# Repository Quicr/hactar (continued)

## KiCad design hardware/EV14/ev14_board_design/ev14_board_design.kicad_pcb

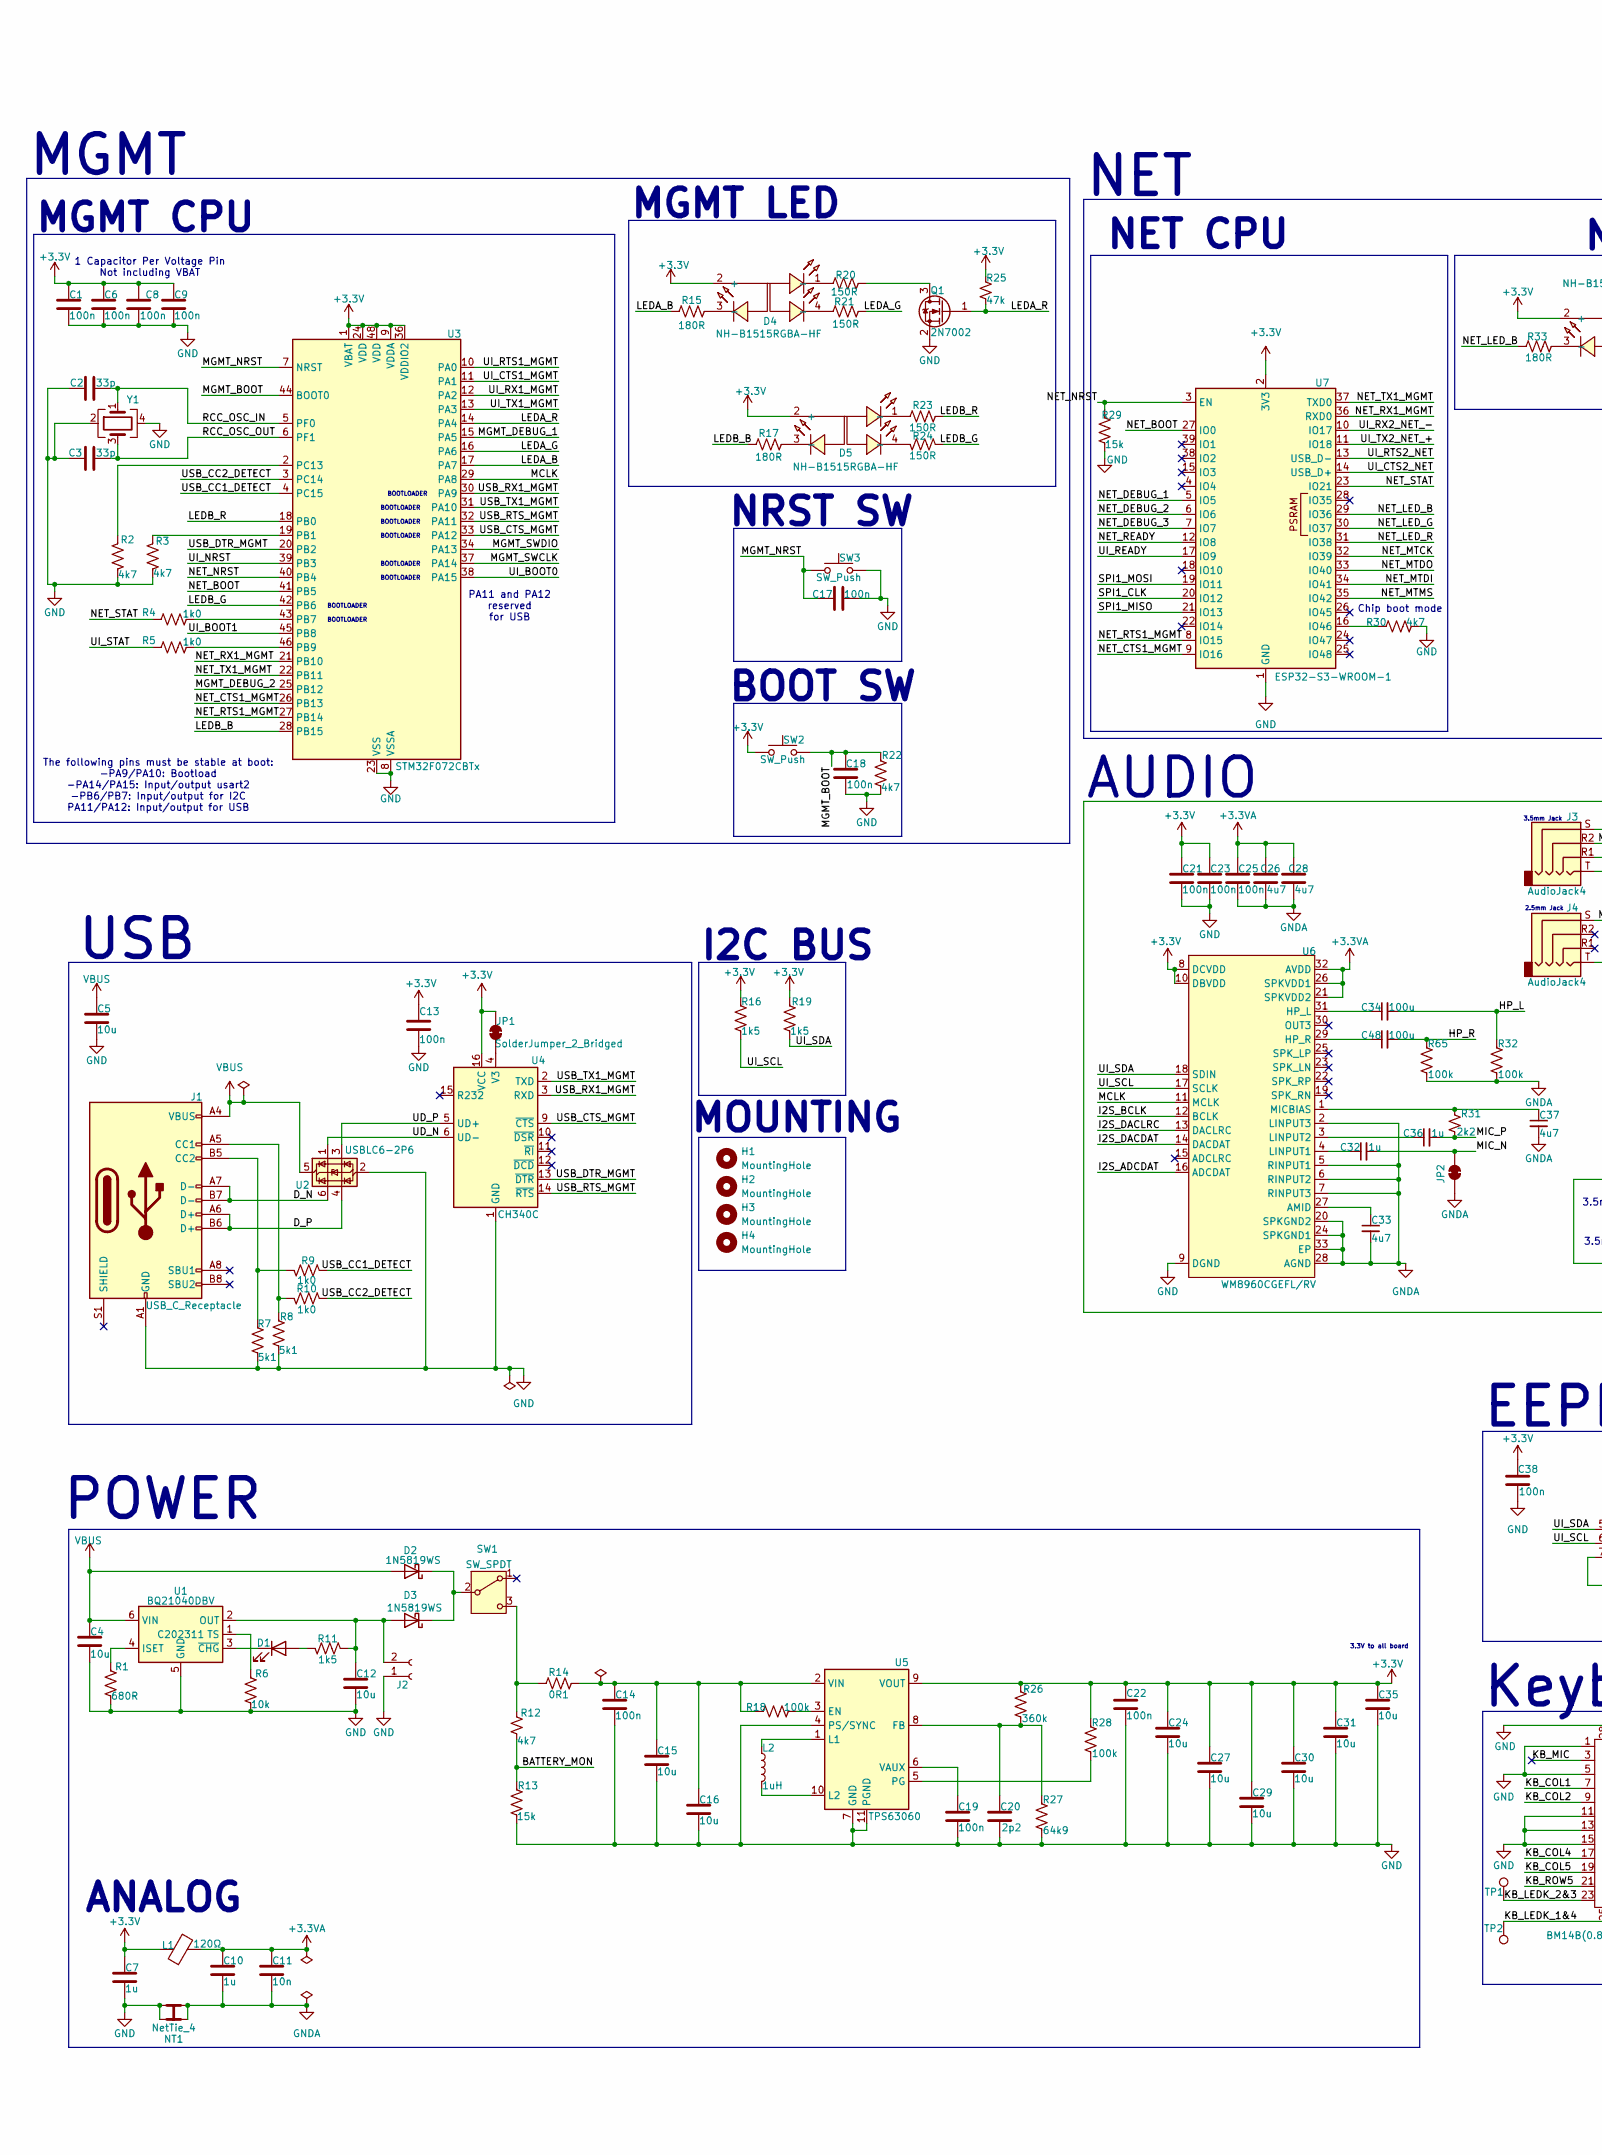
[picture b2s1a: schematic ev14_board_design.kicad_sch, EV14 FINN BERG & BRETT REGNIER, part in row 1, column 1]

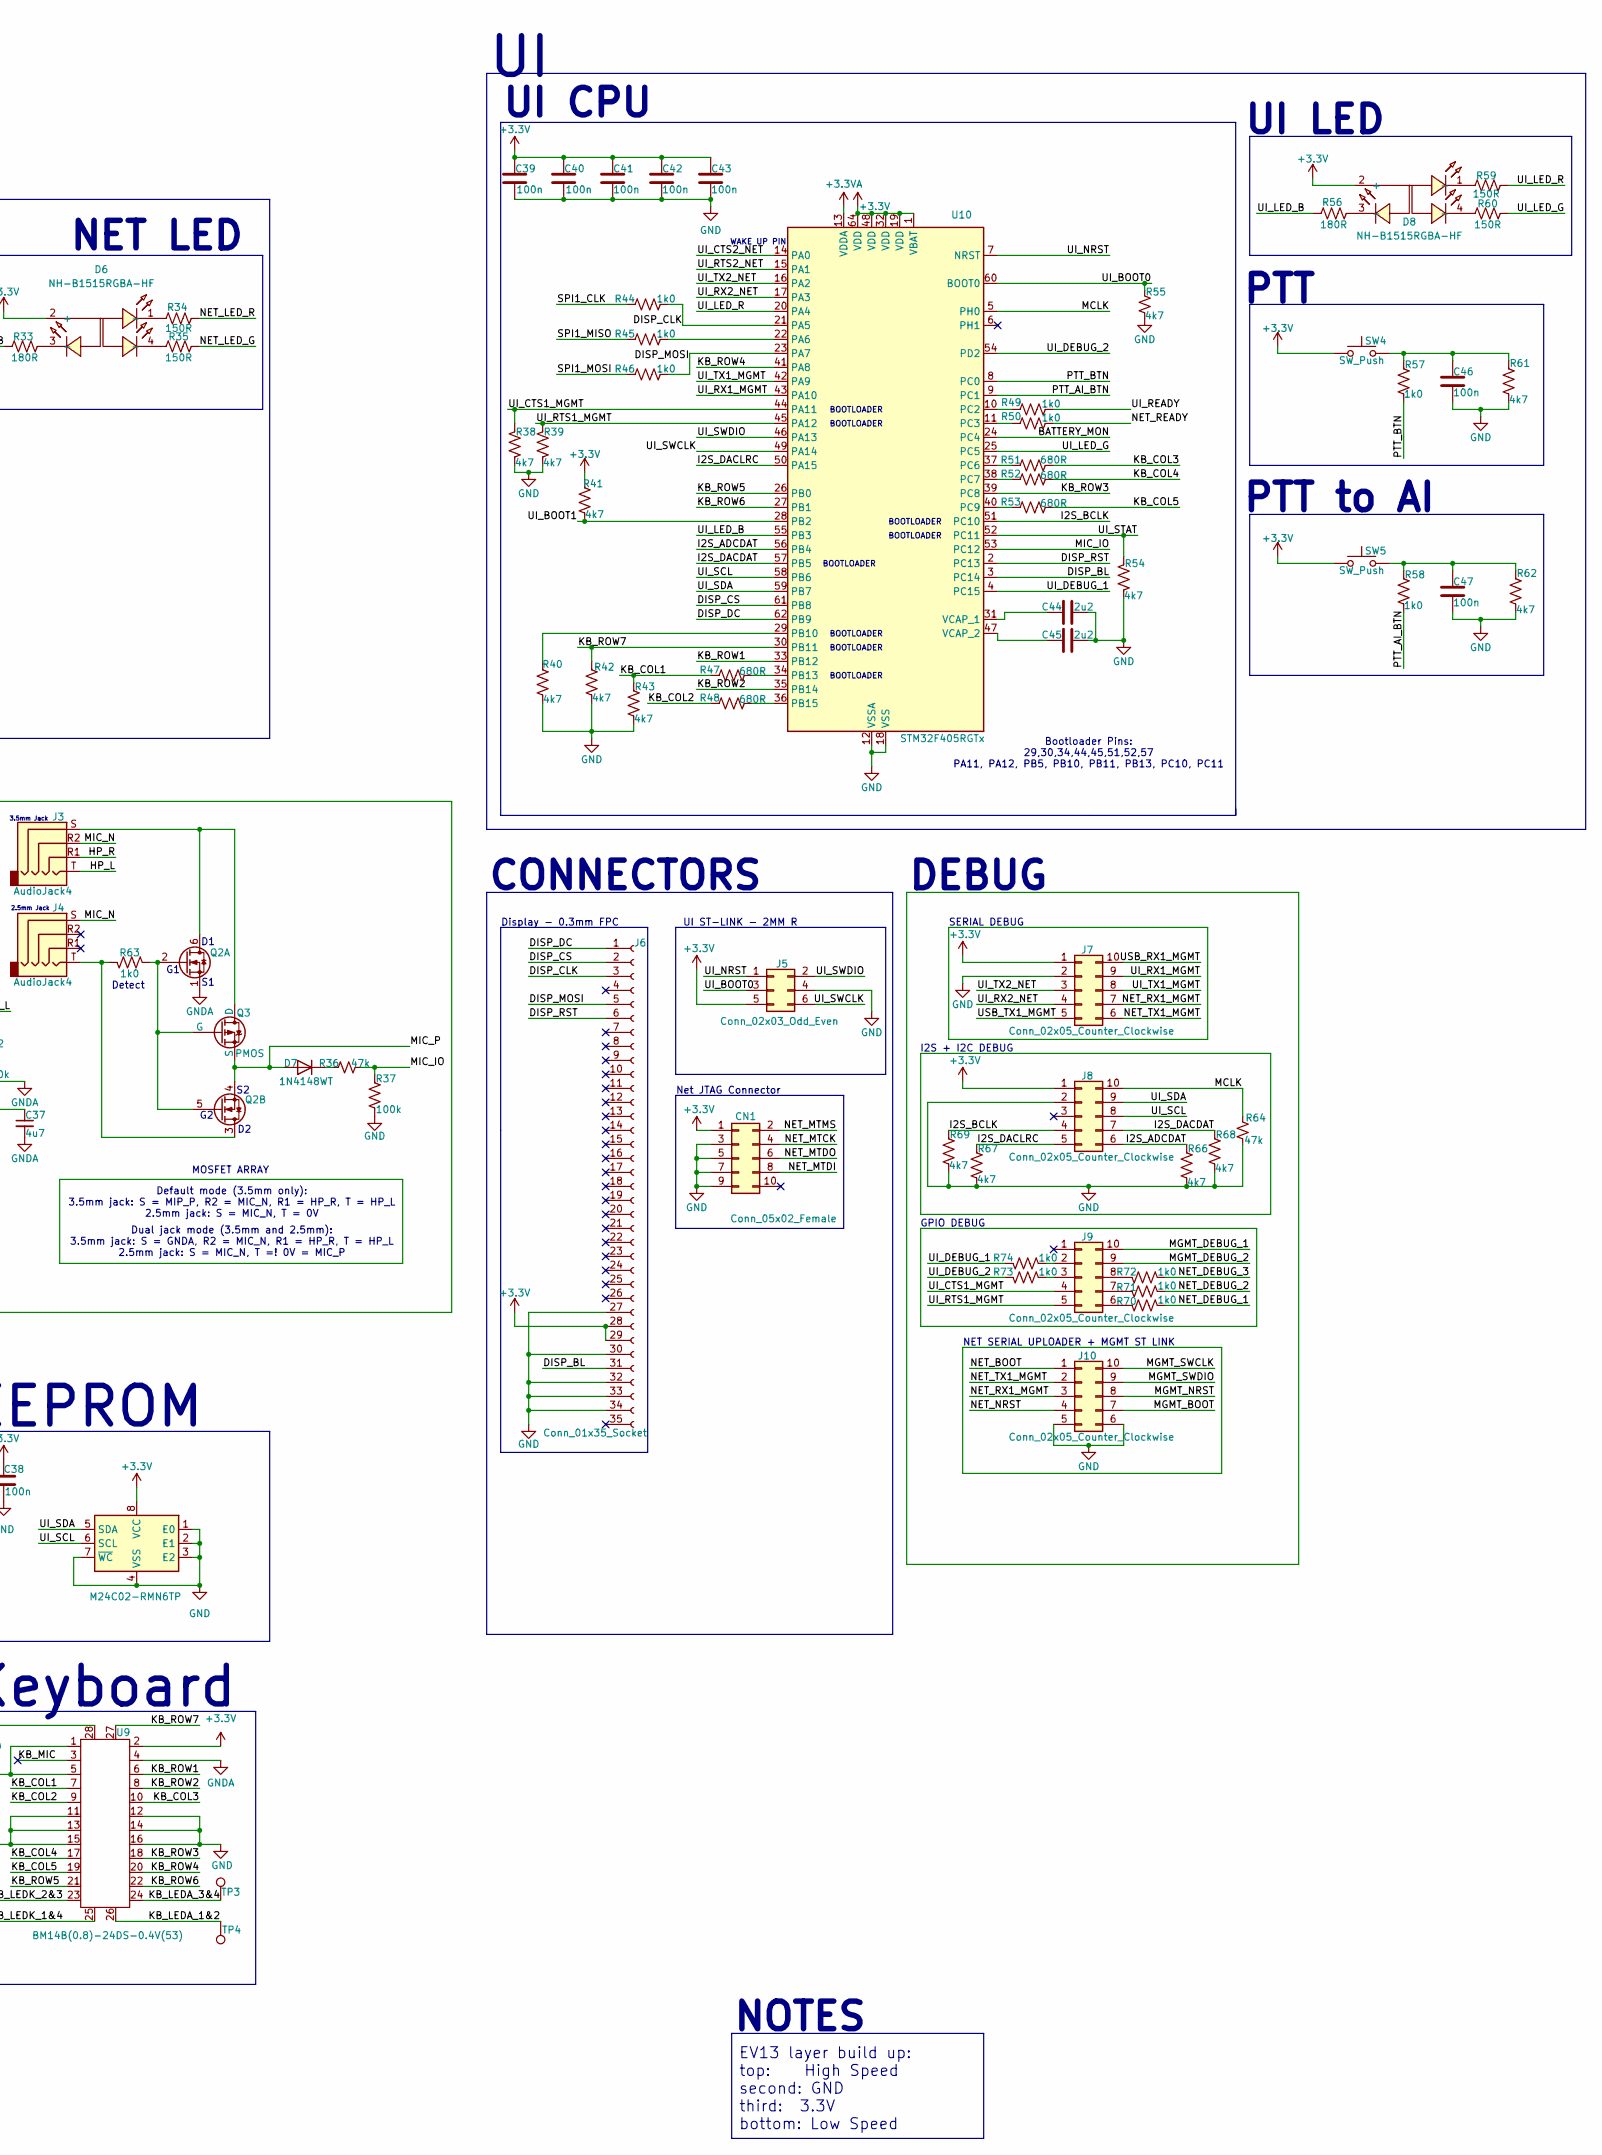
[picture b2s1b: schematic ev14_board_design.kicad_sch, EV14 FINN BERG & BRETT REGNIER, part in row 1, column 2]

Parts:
C1, C6, C8, C9, C13, C17, C18, C21, C23, C25, C38, C39, C40, C41, C42, C43, C46, C47: 100n; C_0402_1005Metric; JLCPCB Part # C1525
C2, C3: 33p; C_0805_2012Metric; JLCPCB Part # C107115
C4, C5, C12: 10u; C_0402_1005Metric; JLCPCB Part # C307415
C7, C10, C32, C36: 1u; C_0402_1005Metric; JLCPCB Part # C52923
C11: 10n; C_0402_1005Metric; JLCPCB Part # C15195
C14, C19, C22: 100n; C_0805_2012Metric; JLCPCB Part # C85866
C15, C16, C24, C27, C29, C30, C31, C35: 10u; C_0805_2012Metric; JLCPCB Part # C83061
C20: 2p2; C_0805_2012Metric; JLCPCB Part # C519933
C26, C28, C33, C37: 4u7; C_0402_1005Metric; JLCPCB Part # C23733
C34, C48: 100u; C_1206_3216Metric; JLCPCB Part # C15008
C44, C45: 2u2; C_0402_1005Metric; JLCPCB Part # C12530
CN1: Conn_05x02_Female; IDC-SMD_10P-P1.27_X1270WVS-2X05B-6TV01; JLCPCB Part # C2962222
D1: LED; D_0805_2012Metric; JLCPCB Part # C130114
D2, D3: 1N5819WS; D_SOD-323; JLCPCB Part # C191023
D4, D5, D6, D8: NH-B1515RGBA-HF; LED-ARRAY-SMD_4P-L1.6-W1.5-TL_NH-B1515RGBA; JLCPCB Part # C2874115
D7: 1N4148WT; D_SOD-523; JLCPCB Part # C27748
H1, H2, H3, H4: MountingHole; MountingHole_2.7mm_M2.5
J1: USB_C_Receptacle; USB-C_SMD-TYPE-C-31-M-12; JLCPCB Part # C165948
J2: Conn_01x02_Socket; JST_PH_S2B-PH-SM4-TB_1x02-1MP_P2.00mm_Horizontal; JLCPCB Part # C295747
J3: AudioJack4; AUDIO-SMD_PJ-320D; JLCPCB Part # C431535
J4: AudioJack4; AUDIO-SMD_PJ-242; JLCPCB Part # C431536
J5: Conn_02x03_Odd_Even; HDR-SMD_6P-P2.54-V-M-R2-C3-LS7.5-2; JLCPCB Part # C3294461
J6: Conn_01x35_Socket; CONN-SMD_HCTL_HC-FPC-03-09-35RLTAG; JLCPCB Part # C5213722
J7, J8, J9, J10: Conn_02x05_Counter_Clockwise; HDR-SMD_10P-P2.54-V-F-R2-C5-LS7.1-1; JLCPCB Part # C3975150
JP1: SolderJumper_2_Bridged; SolderJumper-2_P1.3mm_Bridged_RoundedPad1.0x1.5mm
JP2: SolderJumper_2_Bridged; NetTie-2_SMD_Pad0.5mm
L1: 120Ω; L_0603_1608Metric; JLCPCB Part # C127301
L2: 1uH; MCL2016A1R0MT; JLCPCB Part # C370013
NT1: NetTie_4; NetTie-4_SMD_Pad0.5mm
Q1: 2N7002; SOT-23; JLCPCB Part # C8545
Q2: Q_Dual_NMOS_S1G1D2S2G2D1; SOT-363_L2.1-W1.3-P0.65-LS2.3-BL; JLCPCB Part # C5362112
Q3: PMOS; SOT-23-3_L2.9-W1.3-P1.90-LS2.4-BR; JLCPCB Part # C181091
R1, R47, R48, R51, R52, R53: 680R; R_0402_1005Metric; JLCPCB Part # C25130
R2, R3, R12, R22, R30, R38, R39, R40, R41, R42, R43, R54, R55, R61, R62, R66, R67, R68, R69: 4k7; R_0402_1005Metric; JLCPCB Part # C25900
R4, R5, R9, R10, R44, R45, R46, R49, R50, R57, R58, R63, R70, R71, R72, R73, R74: 1k0; R_0402_1005Metric; JLCPCB Part # C11702
R6: 10k; R_0402_1005Metric; JLCPCB Part # C25744
R7, R8: 5k1; R_0402_1005Metric; JLCPCB Part # C25905
R11, R16, R19: 1k5; R_0402_1005Metric; JLCPCB Part # C25867
R13, R29: 15k; R_0402_1005Metric; JLCPCB Part # C25756
R14: 0R1; R_0603_1608Metric; JLCPCB Part # C111027
R15, R17, R33, R56: 180R; R_0402_1005Metric; JLCPCB Part # C25087
R18, R28, R32, R37, R65: 100k; R_0402_1005Metric; JLCPCB Part # C25741
R20, R21, R23, R24, R34, R35, R59, R60: 150R; R_0402_1005Metric; JLCPCB Part # C25082
R25, R36, R64: 47k; R_0402_1005Metric; JLCPCB Part # C25792
R26: 360k; R_0402_1005Metric; JLCPCB Part # C45956
R27: 64k9; R_0402_1005Metric; JLCPCB Part # C26984
R31: 2k2; R_0402_1005Metric; JLCPCB Part # C25879
SW1: SW_SPDT; SW-TH_SS-12D11G5R; JLCPCB Part # C388633
SW2, SW3: SW_Push; SW-SMD_YIYUAN_YTS1C003XXX; JLCPCB Part # C5188566
SW4, SW5: SW_Push; SW-SMD_L6.0-W6.0-LS6.6; JLCPCB Part # C97448
TP1, TP2, TP3, TP4: TestPoint; TestPoint_THTPad_D2.0mm_Drill1.0mm
U1: BQ21040DBV; SOT-23-6; JLCPCB Part # C202311
U2: USBLC6-2P6; SOT-666; JLCPCB Part # C2827693
U3: STM32F072CBTx; LQFP-48_7x7mm_P0.5mm; JLCPCB Part # C80488
U4: CH340C; SOIC-16_3.9x9.9mm_P1.27mm; JLCPCB Part # C84681
U5: TPS63060; Texas_S-PWSON-N10_ThermalVias; JLCPCB Part # C48567
U6: WM8960CGEFL/RV; QFN-32-1EP_5x5mm_P0.5mm_EP3.45x3.45mm_ThermalVias; JLCPCB Part # C18752
U7: ESP32-S3-WROOM-1; JLCPCB Part # C2913204
U8: M24C02-RMN6TP; SOIC-8_3.9x4.9mm_P1.27mm; JLCPCB Part # C83836
U9: BM14B(0.8)-24DS-0.4V(53); BM14B(0.B)-24DS-0.4V(53); JLCPCB Part # C9900001863
U10: STM32F405RGTx; LQFP-64_10x10mm_P0.5mm; JLCPCB Part # C15742
Y1: Crystal_GND24; Crystal_SMD_3225-4Pin_3.2x2.5mm; JLCPCB Part # C13738

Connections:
+3.3V: C1.2, C6.2, C7.1, C8.2, C9.2, C13.1, C21.2, C22.1, C23.2, C24.1, C27.1, C29.1, C30.1, C31.1, C35.1, C38.2, C39.1, C40.1, C41.1, C42.1, C43.1, CN1.1, D4.2 (+), D5.2 (+), D6.2 (+), D8.2 (+), J5.5, J6.28, J6.29, J7.1, J8.1, JP1.2 (B), L1.1, R16.1, R19.1, R25.2, R26.2, R28.2, R41.1, SW2.1, SW4.1, SW5.1, U3.1 (VBAT), U3.9 (VDDA), U3.24 (VDD), U3.36 (VDDIO2), U3.48 (VDD), U4.16 (VCC), U5.9 (VOUT), U6.8 (DCVDD), U6.10 (DBVDD), U7.2 (3V3), U8.8 (VCC), U9.2, U10.1 (VBAT), U10.19 (VDD), U10.32 (VDD), U10.48 (VDD), U10.64 (VDD)
+3.3VA: C10.1, C11.1, C25.2, C26.1, C28.1, L1.2, U6.21 (SPKVDD2), U6.26 (SPKVDD1), U6.32 (AVDD), U10.13 (VDDA)
/BATTERY_MON: R12.1, R13.1, U10.24 (PC4)
/DISP_BL: J6.31, U10.3 (PC14)
/DISP_CLK: J6.3, R44.1, U10.21 (PA5)
/DISP_CS: J6.2, U10.61 (PB8)
/DISP_DC: J6.1, U10.62 (PB9)
/DISP_MOSI: J6.5, R46.1, U10.23 (PA7)
/DISP_RST: J6.6, U10.2 (PC13)
/D_N: J1.A7 (D-), J1.B7 (D-), U2.6 (I/O1)
/D_P: J1.A6 (D+), J1.B6 (D+), U2.4 (I/O2)
/HP_L: C34.2, J3.T, R32.2
/HP_R: C48.2, J3.R1, R65.2
/I2S_ADCDAT: J8.6, R66.1, U6.16 (ADCDAT), U10.56 (PB4)
/I2S_BCLK: J8.4, R69.1, U6.12 (BCLK), U10.51 (PC10)
/I2S_DACDAT: J8.7, R68.1, U6.14 (DACDAT), U10.57 (PB5)
/I2S_DACLRC: J8.5, R67.1, U6.13 (DACLRC), U10.50 (PA15)
/KB_COL1: R43.2, R47.1, U9.7
/KB_COL2: R48.1, U9.9
/KB_COL3: R51.2, U9.10
/KB_COL4: R52.2, U9.17
/KB_COL5: R53.2, U9.19
/KB_LEDA_1&2: TP4.1, U9.26
/KB_LEDA_3&4: TP3.1, U9.24
/KB_LEDK_1&4: TP2.1, U9.25
/KB_LEDK_2&3: TP1.1, U9.23
/KB_MIC: U9.3
/KB_ROW1: U9.6, U10.33 (PB12)
/KB_ROW2: U9.8, U10.35 (PB14)
/KB_ROW3: U9.18, U10.39 (PC8)
/KB_ROW4: U9.20, U10.41 (PA8)
/KB_ROW5: U9.21, U10.26 (PB0)
/KB_ROW6: U9.22, U10.27 (PB1)
/KB_ROW7: R42.2, U9.27, U10.30 (PB11)
/LEDA_B: R15.2, U3.17 (PA7)
/LEDA_G: R21.2, U3.16 (PA6)
/LEDA_R: Q1.1 (G), R25.1, U3.14 (PA4)
/LEDB_B: R17.2, U3.28 (PB15)
/LEDB_G: R24.1, U3.42 (PB6)
/LEDB_R: R23.2, U3.18 (PB0)
/MCLK: J8.10, R64.1, U3.29 (PA8), U6.11 (MCLK), U10.5 (PH0)
/MGMT_BOOT: C18.2, J10.7, R22.2, SW2.2, U3.44 (BOOT0)
/MGMT_DEBUG_1: J9.10, U3.15 (PA5)
/MGMT_DEBUG_2: J9.9, U3.25 (PB12)
/MGMT_NRST: C17.1, J10.8, SW3.1, U3.7 (NRST)
/MGMT_SWCLK: J10.10, U3.37 (PA14)
/MGMT_SWDIO: J10.9, U3.34 (PA13)
/MIC_IO: R36.1, R37.2, U10.53 (PC12)
/MIC_N: C32.2, J3.R2, J4.S, JP2.1 (A)
/MIC_P: C36.2, D7.2 (A), Q2.4 (S), Q3.3 (S), R31.1
/NET_BOOT: J10.1, U3.41 (PB5), U7.27 (IO0)
/NET_CTS1_MGMT: U3.26 (PB13), U7.9 (IO16)
/NET_DEBUG_1: R70.1, U7.5 (IO5)
/NET_DEBUG_2: R71.1, U7.6 (IO6)
/NET_DEBUG_3: R72.1, U7.7 (IO7)
/NET_LED_B: R33.1, U7.29 (IO36)
/NET_LED_G: R35.1, U7.30 (IO37)
/NET_LED_R: R34.1, U7.31 (IO38)
/NET_MTCK: CN1.4, U7.32 (IO39)
/NET_MTDI: CN1.8, U7.34 (IO41)
/NET_MTDO: CN1.6, U7.33 (IO40)
/NET_MTMS: CN1.2, U7.35 (IO42)
/NET_NRST: J10.4, R29.1, U3.40 (PB4), U7.3 (EN)
/NET_READY: R50.1, U7.12 (IO8)
/NET_RTS1_MGMT: U3.27 (PB14), U7.8 (IO15)
/NET_RX1_MGMT: J7.7, J10.3, U3.21 (PB10), U7.36 (RXD0)
/NET_STAT: R4.2, U7.23 (IO21)
/NET_TX1_MGMT: J7.6, J10.2, U3.22 (PB11), U7.37 (TXD0)
/PTT_AI_BTN: R58.1, U10.9 (PC1)
/PTT_BTN: R57.1, U10.8 (PC0)
/RCC_OSC_IN: C2.2, U3.5 (PF0), Y1.1
/RCC_OSC_OUT: C3.2, U3.6 (PF1), Y1.3
/SPI1_CLK: R44.2, U7.20 (IO12)
/SPI1_MISO: R45.2, U7.21 (IO13)
/SPI1_MOSI: R46.2, U7.19 (IO11)
/UD_N: U2.1 (I/O1), U4.6 (UD-)
/UD_P: U2.3 (I/O2), U4.5 (UD+)
/UI_BOOT0: J5.3, R55.1, U3.38 (PA15), U10.60 (BOOT0)
/UI_BOOT1: R41.2, U3.45 (PB8), U10.28 (PB2)
/UI_CTS1_MGMT: J9.4, R38.2, U3.11 (PA1), U10.44 (PA11)
/UI_CTS2_NET: U7.14 (USB_D+), U10.14 (PA0)
/UI_DEBUG_1: R74.2, U10.4 (PC15)
/UI_DEBUG_2: R73.2, U10.54 (PD2)
/UI_LED_B: R56.1, U10.55 (PB3)
/UI_LED_G: R60.1, U10.25 (PC5)
/UI_LED_R: R59.1, U10.20 (PA4)
/UI_NRST: J5.1, U3.39 (PB3), U10.7 (NRST)
/UI_READY: R49.1, U7.17 (IO9)
/UI_RTS1_MGMT: J9.5, R39.2, U3.10 (PA0), U10.45 (PA12)
/UI_RTS2_NET: U7.13 (USB_D-), U10.15 (PA1)
/UI_RX1_MGMT: J7.9, U3.12 (PA2), U10.43 (PA10)
/UI_RX2_NET: J7.4, U10.17 (PA3)
/UI_RX2_NET_-: U7.10 (IO17)
/UI_SCL: J8.8, R16.2, U6.17 (SCLK), U8.6 (SCL), U10.58 (PB6)
/UI_SDA: J8.9, R19.2, U6.18 (SDIN), U8.5 (SDA), U10.59 (PB7)
/UI_STAT: R5.2, R54.2, U10.52 (PC11)
/UI_SWCLK: J5.6, U10.49 (PA14)
/UI_SWDIO: J5.2, U10.46 (PA13)
/UI_TX1_MGMT: J7.8, U3.13 (PA3), U10.42 (PA9)
/UI_TX2_NET: J7.3, U10.16 (PA2)
/UI_TX2_NET_+: U7.11 (IO18)
/USB_CC1_DETECT: R9.1, U3.4 (PC15)
/USB_CC2_DETECT: R10.1, U3.3 (PC14)
/USB_CTS_MGMT: U3.33 (PA12), U4.9 (~CTS)
/USB_DTR_MGMT: U3.20 (PB2), U4.13 (~DTR)
/USB_RTS_MGMT: U3.32 (PA11), U4.14 (~RTS)
/USB_RX1_MGMT: J7.10, U3.30 (PA9), U4.3 (RXD)
/USB_TX1_MGMT: J7.5, U3.31 (PA10), U4.2 (TXD)
GND: C1.1, C2.1, C3.1, C4.2, C5.2, C6.1, C7.2, C8.1, C9.1, C12.2, C13.2, C14.2, C15.2, C16.2, C17.2, C18.1, C19.2, C20.2, C21.1, C22.2, C23.1, C24.2, C27.2, C29.2, C30.2, C31.2, C35.2, C38.1, C39.2, C40.2, C41.2, C42.2, C43.2, C44.1, C45.1, C46.2, C47.2, CN1.3, CN1.5, CN1.7, CN1.9, J1.A1 (GND), J1.A12 (GND), J1.B1 (GND), J1.B12 (GND), J2.1, J5.4, J6.27, J6.30, J6.32, J6.33, J6.34, J7.2, J8.2, J10.5, J10.6, NT1.1, NT1.3, Q1.2 (S), R1.2, R2.1, R3.1, R6.2, R7.1, R8.1, R13.2, R22.1, R27.1, R29.2, R30.2, R37.1, R38.1, R39.1, R40.1, R42.1, R43.1, R54.1, R55.2, R61.1, R62.1, R64.2, R66.2, R67.2, R68.2, R69.2, SW3.2, U1.5 (GND), U2.2 (GND), U3.8 (VSSA), U3.23 (VSS), U3.35 (VSS), U3.47 (VSS), U4.1 (GND), U5.4 (PS/SYNC), U5.7 (GND), U5.11 (PGND), U6.9 (DGND), U7.1 (GND), U7.40 (GND), U7.41 (GND), U8.1 (E0), U8.2 (E1), U8.3 (E2), U8.4 (VSS), U8.7 (~WC), U9.1, U9.5, U9.11, U9.12, U9.13, U9.14, U9.15, U9.16, U9.28, U10.12 (VSSA), U10.18 (VSS), U10.63 (VSS), Y1.2, Y1.4
GNDA: C10.2, C11.2, C25.1, C26.2, C28.2, C33.2, C37.2, JP2.2 (B), NT1.2, NT1.4, Q2.1 (S), R32.1, R65.1, U6.2 (LINPUT3), U6.5 (RINPUT1), U6.6 (RINPUT2), U6.7 (RINPUT3), U6.20 (SPKGND2), U6.24 (SPKGND1), U6.28 (AGND), U6.33 (EP), U9.4
unnamed: C46.1, R57.2, R61.2, SW4.2
unnamed: C47.1, R58.2, R62.2, SW5.2
unnamed: D1.2 (A), R11.2
unnamed: D1.1 (K), U1.3 (~CHG)
unnamed: D2.1 (K), D3.1 (K), SW1.2 (B)
unnamed: C12.1, D3.2 (A), J2.2, R11.1, U1.2 (OUT)
unnamed: D4.1 (-), R20.1
unnamed: D4.3 (-), R15.1
unnamed: D4.4 (-), R21.1
unnamed: D5.1 (-), R23.1
unnamed: D5.3 (-), R17.1
unnamed: D5.4 (-), R24.2
unnamed: D6.1 (-), R34.2
unnamed: D6.3 (-), R33.2
unnamed: D6.4 (-), R35.2
unnamed: D7.1 (K), R36.2
unnamed: D8.1 (-), R59.2
unnamed: D8.3 (-), R56.2
unnamed: D8.4 (-), R60.2
unnamed: J1.A5 (CC1), R8.2, R10.2
unnamed: J1.B5 (CC2), R7.2, R9.2
unnamed: J9.2, R74.1
unnamed: J9.3, R73.1
unnamed: J9.6, R70.2
unnamed: J9.7, R71.2
unnamed: J9.8, R72.2
unnamed: JP1.1 (A), U4.4 (V3)
unnamed: Q1.3 (D), R20.2
unnamed: J3.S, Q2.6 (D), Q3.1 (D)
unnamed: Q2.2 (G), Q2.5 (G), Q3.2 (G), R63.1
unnamed: J4.T, Q2.3 (D), R63.2
unnamed: R12.2, R14.1, SW1.3 (C)
unnamed: R1.1, U1.4 (ISET)
unnamed: R6.1, U1.1 (TS)
unnamed: R3.2, U3.19 (PB1)
unnamed: R4.1, U3.43 (PB7)
unnamed: R5.1, U3.46 (PB9)
unnamed: R2.2, U3.2 (PC13)
unnamed: R18.2, U5.3 (EN)
unnamed: C20.1, R26.1, R27.2, U5.8 (FB)
unnamed: L2.1, U5.1 (L1)
unnamed: L2.2, U5.10 (L2)
unnamed: R28.1, U5.5 (PG)
unnamed: C19.1, U5.6 (VAUX)
unnamed: C14.1, C15.1, C16.1, R14.2, R18.1, U5.2 (VIN)
unnamed: C33.1, U6.27 (AMID)
unnamed: C34.1, U6.31 (HP_L)
unnamed: C48.1, U6.29 (HP_R)
unnamed: C32.1, U6.4 (LINPUT1)
unnamed: C36.1, U6.3 (LINPUT2)
unnamed: C37.1, R31.2, U6.1 (MICBIAS)
unnamed: R30.1, U7.16 (IO46)
unnamed: R45.1, U10.22 (PA6)
unnamed: R40.2, U10.29 (PB10)
unnamed: R47.2, U10.34 (PB13)
unnamed: R48.2, U10.36 (PB15)
unnamed: R49.2, U10.10 (PC2)
unnamed: R50.2, U10.11 (PC3)
unnamed: R51.1, U10.37 (PC6)
unnamed: R52.1, U10.38 (PC7)
unnamed: R53.1, U10.40 (PC9)
unnamed: C44.2, U10.31 (VCAP_1)
unnamed: C45.2, U10.47 (VCAP_2)
VBUS: C4.1, C5.1, D2.2 (A), J1.A4 (VBUS), J1.A9 (VBUS), J1.B4 (VBUS), J1.B9 (VBUS), U1.6 (VIN), U2.5 (VBUS)

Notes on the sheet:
MGMT
BOOTLOADER
MOSFET ARRAY
NET CPU
MGMT CPU
WAKE UP PIN
PTT to AI
NET
POWER
CONNECTORS
MOUNTING
NET LED
UI CPU
Bootloader Pins: 29,30,34,44,45,51,52,57 PA11, PA12, PB5, PB10, PB11, PB13, PC10, PC11
UI ST-LINK - 2MM R
Chip boot mode
Net JTAG Connector
NRST SW
The following pins must be stable at boot: -PA9/PA10: Bootload -PA14/PA15: Input/output usart2 -PB6/PB7: Input/output for I2C PA11/PA12: Input/output for USB
3.5mm Jack
EV13 layer build up: top: High Speed second: GND third: 3.3V bottom: Low Speed
NET SERIAL UPLOADER + MGMT ST LINK
AUDIO
PTT
BOOT SW
PA11 and PA12 reserved for USB
EEPROM
I2C BUS
USB
2.5mm Jack
Default mode (3.5mm only): 3.5mm jack: S = MIP_P, R2 = MIC_N, R1 = HP_R, T = HP_L 2.5mm jack: S = MIC_N, T = 0V
Detect
MGMT LED
3.3V to all board
DEBUG
NOTES
Keyboard
Display - 0.3mm FPC
GPIO DEBUG
Dual jack mode (3.5mm and 2.5mm): 3.5mm jack: S = GNDA, R2 = MIC_N, R1 = HP_R, T = HP_L 2.5mm jack: S = MIC_N, T =! 0V = MIC_P

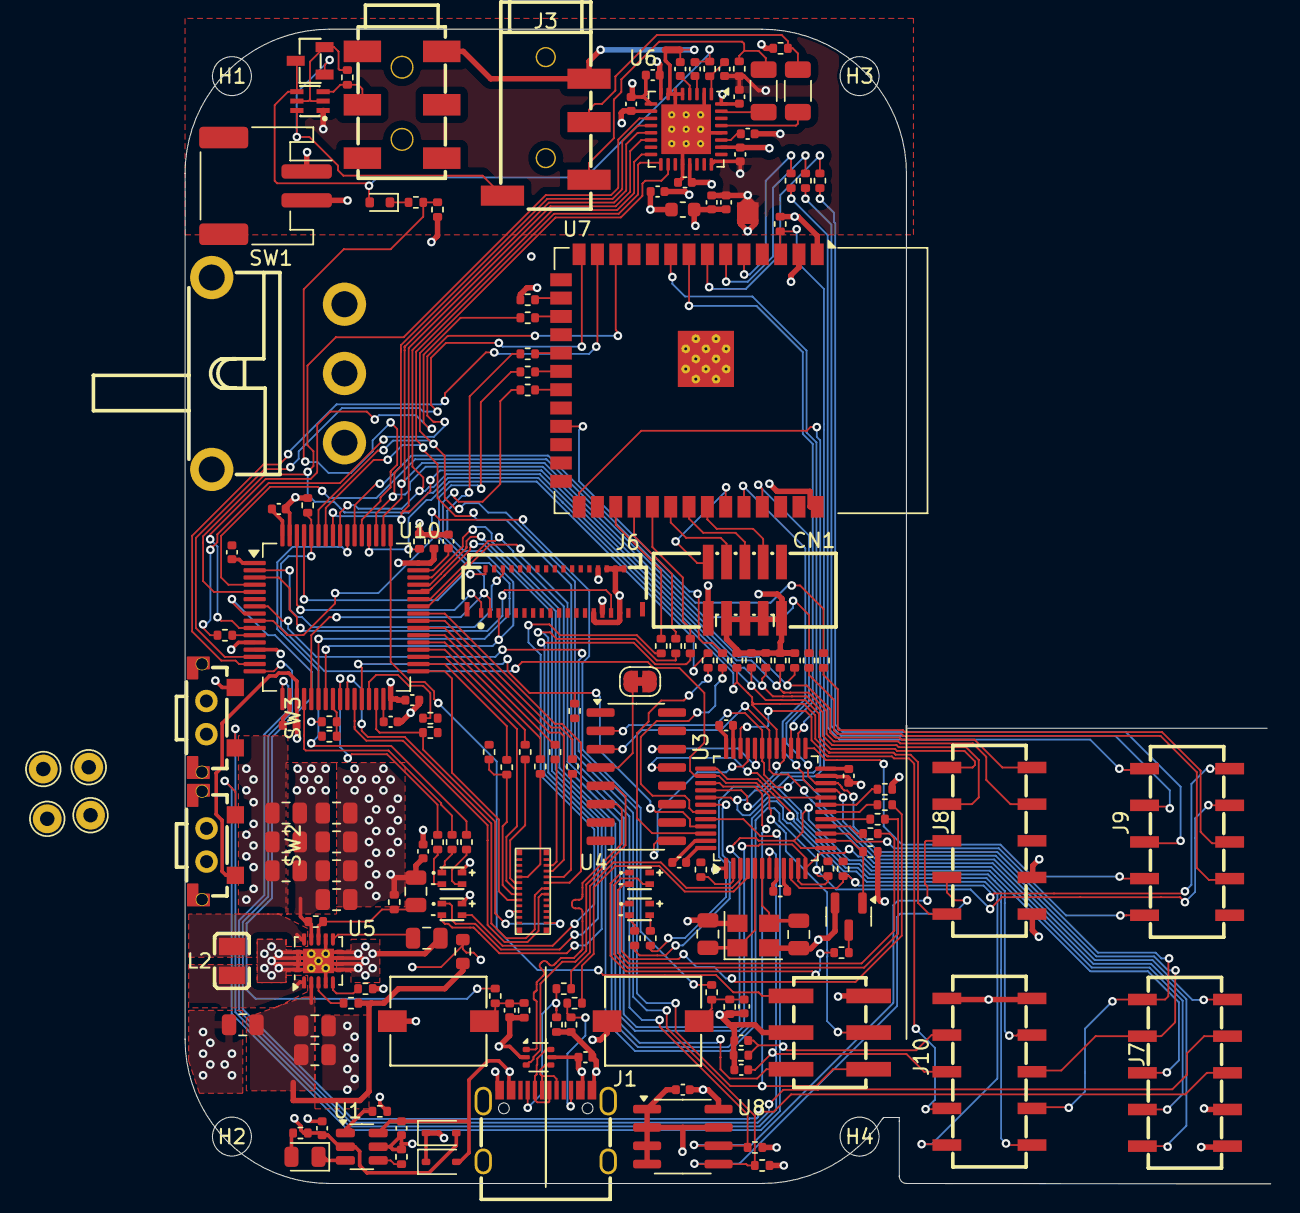
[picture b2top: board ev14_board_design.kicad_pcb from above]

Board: 4 copper layers, 75.2 x 80.0 mm, 173 parts (0 on the bottom side), 171 nets.
